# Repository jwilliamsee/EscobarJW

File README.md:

# EscobarJW
Todo el texto no está justificado porque el formato Markdown usado en esta plataforma no lo permite, en algunos párrafos si está justificado porque uso html pero en algunas estructuras de texto aquí presentadas no es posible aplicarlo.
### Información.

#### En la carpeta "**Certificado-Ingeniería**"

<p align="justify">Está el certificado de estudios de la carrera universitaria en Ingeniería Electromecánica con especialidad en la industria aeroespacial, específicamente enfocado a diseño CAD y electrónica.</p>

------------
#### En la carpeta "**LoQueHiceEn-IER-UNAM**". 
<p align="justify">Se encuentran 7 dispositivos electrónicos en los que participé durante la residencia profesional y posteriormente con un contrato laboral para seguir colaborando, lo planteado inicialmente era establecer una forma de documentar los dispositivos electrónicos que se tenían avanzados, con un estándar de documentación que se adaptara a etapas de desarrollo enfocado a documentar todo lo que se había hecho y faltaba por hacer en cada uno. El problema a solucionar era que cuando otros estudiantes llegaban para hacer residencias o prácticas profesionales y avanzaban en alguno de los dispositivos, no dejaban documentación completa de lo que avanzaban o no entregaban algo de lo que hacían, los diagramas estaban incompletos o estaban pero no los archivos fuentes para editar y modicar, los códigos de programación no estaban para editarlos y se tenía que contactar al estudiante que lo empezó y con suerte rescatarlo para futuras mejoras, el hardware se tenía que reconectar y reestructurar y pasar por los mismos errores que quizá pasó el primer estudiante en las primeras versiones y a todo eso con el estándar de documentación que investigué y finalmentente elegí con algunas adaptaciones necesarias para lo que se requería, hicieron que mis aportaciones fueran las siguientes:.</p>

	Solución y aportes propuestos por mi:
- [x] Investigación y elección del estándar de documentación para los dispositivos electrónicos del IER-UNAM.
- [x] Elección de la forma de documentación en cuanto a Hardware adaptada al estándar "Open-Know-How".
[**Open-Know-How**](https://www.internetofproduction.org/open-know-how)
- [x] Gestionar la documentación en todos los dispositvos hechos y por hacer, para el control y cumplimiento de cada avance hechos por otros compañeros.
- [x] Apliqué el estándar de documentación a un dispositivo como prueba y posteriormente se usó como ejemplo para que los otros compañeros lo aplicaran al dispositivo que estaban desarrollando.
- [x] Instructivos para documentar sus avances en esta plataforma en forma de repositorio por cada dispositivo desde Windows y Linux.
- [x] Apoyo de todo el proceso para documentar, con videos del paso a paso.
[**Serie de videos hechos por mi**](https://github.com/jwilliamsee/DocumentarGithub/blob/main/VideosDocGit/LinksDeVideos.md)

**Cabe mencionar que en cada dispositivo participó más de una persona, yo participé en todos para verificar que se aplicara lo que propuse, apoyar en las dudas de como documentar con el estándar elegido, probar y modificar código básico en Python, C++ y Micropython (yo no programaba), mis participaciones también se centraban en la parte del Hardware electrónico.**
- [x] Al mismo tiempo de la investigación, desarrollo, aplicación del estándar y seguimiento a cada dispositivo, también me ocupaba en el desarrollo del dispositivo H2O, sólo se tenía el código o programación. [**Dispositivo H2O**](https://github.com/jwilliamsee/EscobarJW/tree/main/LoQueHiceEn-IER-UNAM/SensorH2O1)
- [x] Diseñé la carcasa del dispositivo H2O, diseñé la placa PCB, hice el diagrama de conexión, diagrama de conexión animada (pictograma), modifiqué la programación, generé archivos para impresión en 3D, instructivo de uso del dispositivo, instructivo de ensamble, pruebas del funcionamiento y los archivos entregables.
------------
## Parte de mi trabajo en el IER-UNAM
<p align="justify">Durante el tiempo que trabajé en el **Instituto de Energías Renovables** (IER-UNAM), posterior a los 6 meses que estuve en residencia profesional, seguí trabajando en los dispositivos, hasta liberar documentación necesaria en cada uno, modificar archivos trabajados por otros compañeros, pruebas de mando a distancia con una plataforma Internet Of Things (IOT), entre otras cosas.<p/>

#### A continuación una breve descripción de cada dispositivo en los que apoyé y lo que aporté:
	Dispositivo DTHIS: Mide Temperatura, Humedad, Iluminación y Sonido (nivel sonoro).
[**Dispositivo DTHIS**](https://github.com/jwilliamsee/EscobarJW/tree/main/LoQueHiceEn-IER-UNAM/DTHIS)

**Aportes:**
- Gestión de la documentación.
- Diseño de PCB como complemento del existente.
- Rediseño del diagrama de conexión.
- Réplica de un segundo dispositivo DTHIS para comprobar que ya era factible y viable su reprodución (funcionó correctamente el segundo).
------------
	Dispositivo FactorDePotencia: Mide Factor de potencia y consumo de energía eléctrica.
[**Dispositivo FactorDePotencia**](https://github.com/jwilliamsee/EscobarJW/tree/main/LoQueHiceEn-IER-UNAM/FactorDePotencia)

**Aportes:**
- Avances en la gestión de documentación.
- Diseño CAD de la carcasa del dispositivo.
- Rediseño del PCB existente.
- Diseño del diagrama de conexión.
------------
	Repositorio TemplateSADs: Plantilla para usarlo en la documentación de otros dispositivos.
[**Repositorio TemplateSADs**](https://github.com/jwilliamsee/EscobarJW/tree/main/LoQueHiceEn-IER-UNAM/TemplateSADs)

**Aportes:**
###### Formato elegido, previamente investigado para ser adaptado a otros dispositivos.
------------
	 Dispositivo WindSensor: Mide la rapidez del viento.
[**Dispositivo WindSensor**](https://github.com/jwilliamsee/EscobarJW/tree/main/LoQueHiceEn-IER-UNAM/WindSensor)

**Aportes:**
- Investigación de la implementación del sensor elegido.
- Modificar la programación para lectura del viento (ya existía un reporte trabajado).
- Diagrama de conexión.
- Pruebas de su funcionamiento bajo condiciones necesarias de operación.
- Montaje de banco de prueba básico.
------------
	Dispositivo abb_energia: Equipo industrial que mide corriente eléctrica trifásica, factor de potencia, potencia activa, potencia aparente, potencia reactiva y voltaje.
[**Dispositivo abb_energia**](https://github.com/jwilliamsee/EscobarJW/tree/main/LoQueHiceEn-IER-UNAM/abb_energia)

**Aportes:**
- Gestión de la documentación (revisión).
- Asesoría en la documentación.
------------
	 Dispositivo sensor_flujo_calor: Mide el flujo de calor de superficies planas con ciertas condiciones.
[**Dispositivo sensor_flujo_calor**](https://github.com/jwilliamsee/EscobarJW/tree/main/LoQueHiceEn-IER-UNAM/sensor_flujo_calor)

**Aportes:**
- Gestión de la documentación (revisión).
- Asesoría en la documentación.
------------

##### Existen otros dispositivos y repositorios que ya no están en mi dominio, de igual forma estos dispositivos que se presentan se siguieron avanzando y participé en la gestión de documentación, manufactura, diseño, étc.
------------

####  En la carpeta "Proyecto_Residencia_Profesional" se encuentra el reporte de residencia que entregué al Instituto Tecnológico de Ensenada (ITE) y las evaluacioenes de la misma, por el Dr. Barrios, mi jefe inmediato durante la residencia, también se encuentra la carta de término de residencia emitida por el Instituto de Energías Renovables (IER-UNAM).
[**Reporte de residencia profesional**](https://github.com/jwilliamsee/EscobarJW/tree/main/Proyecto_ResidenciaProfesional)

------------

####  En la carpeta "Proyecto_ServicioSocial" se encuentran archivos del proyecto que propuse durante el servicio social: "Cálculo de cargas térmicas para la elección adecuada del sistema de aire acondicionado", al ver una oportunidad de mejora en la biblioteca del Instituto Tecnológico de Ensenada por el exceso de calor que se acumulaba y no contar con aire acondicionado.
#### El objetivo principal del proyecto fue calcular la carga térmica total de la planta baja del centro de información, para diseñar un ambiente de confort, los resultados son cálculos en toneladas de refrigeración para elegir los equipos comerciales de aire acondicionado y las posibles distribuciones de los mismos en la planta baja, se entregó un reporte técnico y la memoria de cálculo para ser considerado al momento de acondicionar la biblioteca y no sobredimensionar en exceso los equipos y que posteriormente represente un exceso en el consumo de energía eléctrica. El proyecto está relacionado con **Refrigeración, aire acondicionado** y **Transferencia de calor**.

[**Proyecto servicio social**](https://github.com/jwilliamsee/EscobarJW/tree/main/Proyecto_ServicioSocial)

**Aportes:**
- [x] Cálculo de cargas térmicas por infiltración.
- [x] Cálculo de cargas térmicas por radiación.
- [x] Cálculo de cargas térmicas por equipos.
- [x] Cálculo de condiciones de confort con tablas psicométricas.
- [x] Entrega de memoria de cálculos en Excel.
- [x] Recomendaciones en la elección de los equipos de aire acondicionado.

------------
# Algunos diseños CAD, diagramas electrónicos y Diseño PCB en los que he trabajado, existen otros PCB que por confidencialidad de mi empleador freelancer no puedo mostrar:

### Máquina de serigrafía
#### Diseño de máquina para serigrafía con ecuaciones de movimiento.

------------

------------
### Dispositivo THIS
#### Diagrama de conexión electrónica del dispositivo THIS, parte del trabajo en el IER-UNAM:

------------
#### Pictograma de conexión (conexión animada) del mismo dispositivo THIS:

------------
#### Montaje en pruebas del dispositivo THIS:

------------
#### Diseño de PCB como complemento del dispositivo THIS:

------------
### Dispositivo factor de potencia
#### Rediseño de PCB del dispositivo Factor de potencia, parte del trabajo en el IER-UNAM:

------------
#### Diseño CAD de carcasa del dispositivo Factor de potencia, parte del trabajo en el IER-UNAM:

------------
### Dispositivo H2O
#### Diseño CAD de la carcasa del dispositivo H2O

------------

------------

------------
#### Diagrama electrónico del dispositivo H2O

------------
#### Diseño PCB del dispositivo H2O

------------
#### Representación general para el diseño del dispositivo H2O

------------
#### Planos de la carcasa del dispositivo H20

------------

------------
### Trabajando como Freelancer en tiempos libres
#### Diseño de PCB1

------------

------------
#### Diseño de PCB2

------------

------------
### Simulación de análisis estático
#### Análisis estático de una caldera

------------

------------

------------

------------

------------

------------
#### Análisis estático de un sujetador mecánico 

------------

------------

------------

------------

------------

------------

------------

------------

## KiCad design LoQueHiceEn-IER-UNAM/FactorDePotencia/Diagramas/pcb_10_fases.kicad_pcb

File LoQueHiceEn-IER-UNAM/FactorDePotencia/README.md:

# Dispositivo Factor de potencia

# 1.0 Introducción

El futuro de la humanidad y del planeta dependen de la manera en la que produzcamos energía: un sistema energético fiable, asequible y descarbonizado es fundamental.
Las energías renovables son fuentes de energía limpias, inagotables y crecientemente competitivas. Se diferencian de los combustibles fósiles principalmente en su diversidad, abundancia y potencial de aprovechamiento en cualquier parte del planeta, pero sobre todo en que no producen gases de efecto invernadero, causantes del cambio climático, ni emisiones contaminantes. Además, sus costes evolucionan a la baja de forma sostenida, mientras que la tendencia general de costes de los combustibles fósiles es la opuesta.
El crecimiento de las energías renovables es imparable, como queda reflejado en las estadísticas aportadas anualmente por la Agencia Internacional de la Energía (AIE): según las previsiones de la AIE, la participación de las renovables en el suministro eléctrico global pasará del 26% en 2018 al 44% en 2040, y proporcionarán 2/3 del incremento de demanda eléctrica registrado en este período, principalmente a través de las tecnologías eólica y fotovoltaica.
De acuerdo a la AIE, la demanda mundial de electricidad aumentará un 70% hasta 2040, elevando su participación en el uso de energía final del 18% al 24% en el mismo período, espoleada principalmente por regiones emergentes (India, China, África, Oriente Medio y el Sureste asiático).
Con lo anterior y compartiendo la idea de utilizar mas las energías limpias, se implementan nuevas formas de controlar los diferentes recursos que se utilizan en el día a día en el Instituto de Energías Renovables-UNAM, se implementarán dispositivos que puedan medir la cantidad de recursos que se consumen como lo son: el agua, la energía eléctrica, humedad, intensidad luminosa, temperatura, entre otras, de un edificio del instituto, con la intención de poder medir cada variable y posteriormente observar cuanto se consume para tratar de reducirlos en gran medida, lo anterior se lleva a cabo con dispositivos electrónicos que están integrados principalmente con sensores y haciendo uso de tecnologías abiertas para los programas y envío de datos a la plataforma IOT Thingsboard para la visualización de gráficos.

### 1.1 Sobre los autores

|Nombre|Instituto/Organización|Email|
| ------------ | ------------ | ------------ |
|Juan Valle Bahena|ITZ|juanvb999@gmail.com|
|Falta |Falta|Falta|
|Guillermo Barrios del Valle|IER-UNAM|gbv@ier.unam.mx|
|Guillermo Ramírez Zúñiga|IER-UNAM|guraz@ier.unam.mx|

------------

# 2. Alcance

El dispositivo Factor de potencia tiene como alcance, en esta etapa, contar con toda la documentación necesaria  e incluso en atapa inicial de pruebas, después de ser trabajado por un grupo de personas se espera que el proyecto tenga todo lo que se necesita para que otras personas puedan entender el funcionamiento y requisitos de operación.

La audiencia a la que está destinada es:

- Por el momento a personal del IER-UNAM que se encuentra trabajando en el proyecto "Edificios demostrativos de diseño bioclimático en clima cálido subhúmedo en el Instituto de Energías Renovables UNAM".

Proyecto número 291600 del Fondo de Sustentabilidad Energética.
- Compañeros que se interesen en aportar al proyecto para mejorar o para replicarlo directamente.

------------

# 3. Conceptos y definiciones

### 3.1 Saber como

Es necesario conocer algunas cosas antes de intentar entender muchos puntos del proyecto, como por ejemplo: lectura de planos electrónicos, diseño CAD, conocimiento medio de electrónica, programación, entre otras.

### 3.2 Diseño

Deberá manejar algún software de diseño por computadora, para modificar, replicar el diseño existente e incluso conocer la sección de ensamble de piezas en el software de su preferencia.

### 3.3 Hacer

Fabricar, construir, ensamblar, imprimir, configurar, programar y compilar códigos.

### 3.4 Open source

Por su traducción al español, "fuente abierta" durante el desarrollo del proyecto se busca que todos los programas a usar, sean de fuente abierta para evitar pagos costosos de Licencia, para cada necesidad existe un software de fuente abierta.

### 3.5 Thingsboard

Es una plataforma de IOT que nos ayuda a visualizar gráficamente las variables que se están midiendo para tener referencias de lo que se está haciendo.

### 3.6 Github

Plataforma web, que sirve como "bodega" para almacenar un proyecto con sus respectivas versiones o modificaciones que pueda sufirir durante el desarrollo, al mismo tiempo ayuda a documentar y a entender la estructura de su funcionamiento.

------------

# 4.0 Especificaciones de la estructura

### 4.1 Introducción

En esta sección se encuentra la estructura general del proyecto, de forma que sea entendible y que se le pueda dar seguimiento para la lectura del mismo y entender que lleva un orden.
Esta forma de estructurar el proyecto es un formato estándar de Open Know-How, cabe mencionar que no es el ideal pero para entender de forma general un proyecto de electrónica es aceptable.
El almacenamiento en Github nos ayuda en todo momento a realizar modificaciones que creemos necesarias y sobre todo a tener control total de los cambios que va sufriendo el proyecto durante el desarrollo, si alguna no nos agrada o no es la correcta, podemos regresar sin ningún problema y dejarlo como antes.

### 4.2 Estructura

### 4.2.1 Formato

El formato de archivo para la documentación del dispositivo es Markdown por su facilidad de uso.
Algunos archivos están en formato PDF pero es necesario para una mejor visualización de los esquemas que se muestran en ese formato.

### 4.2.2 Nombre del archivo

Para los nombres de los archivos, es necesario que no se usen comas, virgulilla o tilde de la ñ, las separaciones de las palabras pueden ser usadas con guiones o sin espacios, pero con una letra mayúscula para saber donde termina e inicia otra palabra, por ejemplo: ArchivoEstructura".
Las extensiones de los archivos pueden ser:

- .json | Para los archivos que se realizaron con EasyEDA.
- .md | Para los archivos que son creados en formato de texto Markdown, M Editor, DILLINGER e incluso el archivo README de Github.
- .fzz | Para los archivos que fueron creados en el software de Fritzing, pictogramas de conexiones.
- .ESTEP | Para los archivos de diseño CAD, que pueden ser visualizados en cualquier software de diseño, es formato general.
- .STL | Para los archivos de impresión, para que el diseño de la carcasa del dispositivo pueda ser visualizado al momento de imprimirlo en 3D.
- .zip | Para los archivos de impresión de la placa o PCB, están comprimidos porque son varios archivos.
- .PDF | Para los archivos que si se guardan en otro formato, posiblemente se moverían mucho las líneas, formas, tablas, imágenes, etc. Los archivos que se encontrarán en el repositorio en este formato serán los planos para el diseño de la carcasa.

### 4.2.3 Vínculos

En algunas secciones de la documentación es necesario nombrar o hacer referencias a rutas externas, pueden ser a imágenes, páginas web entre otras, simplemente se hace uso de los links originales de la web en cuestión, copiando y posteriormente pegando en la sección correspondiente para no tener que buscar de manera externa, deberán dejar espacios entre título o texto para que no existan errores de posición en el archivo de texto final.

#### 4.2.4 Ubicación del repositorio

El repositorio de todo el proyecto se encuentra en Github, las diferentes carpetas y archivos están alojadas en un un solo repositorio, no existe una carpeta raíz, pero sí existe una dirección raíz y es la siguiente:

[**Falta redireccionarlo**]()

### 4.3 Información de la web

La página de presentación del proyecto, está en la sección de Github.

El sitio web del formato estándar para documentar es el siguiente:

[**Falta redireccionarlo**]()

### 4.4 Propiedades descriptivas

### 4.4.1 Título

##### Dispositivo de Factor de potencia
##### Medidor de.....(falta complementar)

### 4.4.2 Descripción

##### Energías renovables
##### Dispositivo pensado para...(falta complementar)

### 4.4.3 Uso previsto

##### Control de variable
###### Informa al usuario el....(falta complementar)

### 4.4.4 Palabras clave

##### Electrónica
##### Dispositivo
##### Faltan poner otras

### 4.4.5 Precauciones y recomendaciones

Son recomendaciones para operar el dispositivo(falta complementar)

### 4.5.6 Contacto primario

**Inv. A tiempo completo:** Dr. Guillermo Barrios del Valle

**Email:** gbv@ier.unam.mx

**Posdoc.:** Dr. Guillermo Ramírez Zúñiga

**Email:** guraz@ier.unam.mx

### 4.5.7 Colaboradores

**Nombre: Juan Valle Bahena** 

**Instituto: Instituto Tecnológico de Zacatepec (ITZ)**

**Email: juanvb999@gmail.com**

**Nombre:**

**Instituto:**

**Email:**

**Nombre:**

**Instituto:**

**Email:**

### 4.5.7 Imagen

Representación gráfica del dispositivo Factor de potencia (**Falta**)

### 4.5.8 Etapa de desarrollo

La etapa en la que se encuentra el desarrollo del dispositivo Factor de potencia, es la de documentación y primeras pruebas.

## Seguimiento de actividades del dispositivo Factor de potencia

|**Actividad**|**Tiempo estimado de ejecución**|**% de avance**|**Pendientes**|**Notas**   |
| :------------: | :------------: | :------------: | :------------: | :------------: |
|**1.**| |   |   |   |
|   |   |   |   |   |
|**2.**|   |   |   |   |
|   |   |   |   |   |
|**3.**|   |   |   |   |
|   |   |   |   |   |
|**4.**|   |   |   |   |
|   |   |   |   |   |
|**5.**|   |   |   |   |
|   |   |   |   |   |
|**6.**|   |   |   |   |
|   |   |   |   |   |
|**7.**|   |   |   |   |
|   |   |   |   |   |
|**8.**|   |   |   |   |
|   |   |   |   |   |
|**9.**|   |   |   |   |
|   |   |   |   |   |
|**10.**|   |   |   |   |
|   |   |   |   |   |
|**11.**|   |   |   |   |
|   |   |   |   |   |
|**12.**|   |   |   |   |
|   |   |   |   |   |
|**13.**|   |   |   |   |
|   |   |   |   |   |
|**14.**|   |   |   |   |
|   |   |   |   |   |
|**15.**|   |   |   |   |
|   |   |   |   |   |
|**16.**|   |   |   |   |
|   |   |   |   |   |
|**17.**|   |   |   |   |
|   |   |   |   |   |
|**18.**|   |   |   |   |
|   |   |   |   |   |
|**19.**|   |   |   |   |
|   |   |   |   |   |
|**20.**|   |   |   |   |
|   |   |   |   |   |

------------

## CHECK-LIST de lo que debe tener el dispositivo
- [ ] Lista de costos
- [ ] SRC completos
- [ ] Pictograma de conexión
- [ ] Esquemático de conexión
- [ ] Archivos de diseño PCB
- [ ] Archivos gerber para el maquinado del PCB
- [ ] Lista de materiales
- [ ] Planos CAD
- [ ] Archivos de diseño CAD
- [ ] Archivos STL para impresión 3D
- [ ] Manual de operación
- [ ] Manual de ensamble
- [ ] Fichas técnicas o datasheet de los módulos, sensores y componentes usados
- [ ] Documento de errores, soluciones y recomendaciones

### 4.5.9 Fue hecho físicamente

El dispositivo aún no se ha hecho de forma práctica en su totalidad, es decir, no se ha llevado a la práctica para comprobar el funcionamiento del dispostivo completo con todos sus componentes.

### 4.5.10 Se ha comprobado la documentación

La réplica del dispositivo usando la estructura aquí mostrada y siguiendo la documentación no se ha realizado, aún está en revisión de estructura de documentación y de archivos factibles para el desarrollo eficiente.

### 4.5.11 Estándares usados

El estándar de documentación completo, no se ha seguido, pero si se ha usado el estándar para esta documentación de Open Know-How, algunos puntos se han omitido porque al no ser la estructura para documentar proyectos electrónicos, existen puntos que salen sobrando o que definitivamente no aplican para este tipo de proyectos.
El link del estándar usado es el siguiente:

[EstandarOpenKnowHow](https://app.standardsrepo.com/MakerNetAlliance/OpenKnowHow/src/branch/master/1#a40dfa47-8bff-4e28-9338-3f808ddfe6ae)

### 4.6 Documentación

### 4.6.1 Punto de entrada de la documentación:

### Carpeta [CAD](https://github.com/Dispositivos-Edificio-Bioclimatico/FactorDePotencia/tree/master/CAD)

En la carpeta CAD se deben poner los archivos .STEP del diseño de la carcasa o de alguna parte física.

En la misma carpeta se deben poner planos en formato PDF y los archivos .STL para visualización.

### Carpeta [Diagramas](https://github.com/Dispositivos-Edificio-Bioclimatico/FactorDePotencia/tree/master/Diagramas)

En la carpeta de Diagramas se debe poner, el esquemático, el diseño de PCB, representaciones gráficas de conexión (pictogramas) y archivo gerber con lo necesario para maquinar el pcb.

### Carpeta [Imagenes](https://github.com/Dispositivos-Edificio-Bioclimatico/FactorDePotencia/tree/master/Imagenes)

En esta carpeta deben ir todas las imagenes que se usaron en los archivos de los manuales y otras imagenes necesarias para el complemento del dispositivo.

### Carpeta [Manuales](https://github.com/Dispositivos-Edificio-Bioclimatico/FactorDePotencia/tree/master/Manuales)

En esta carpeta se debe contener lo siguiente:
1. El manual de operación, para consultarlo antes de iniciar con la replica del dispositivo.
2. El manual de ensamble, de manera gráfica (ilustrativa), se describe de forma general como realizar el ensamble de los componentes del dispositivo.
3. Un manual de errores y soluciones que debe tener algunas sugerencias de operación para operar el dispositivo.

### Carpeta [Materiales](https://github.com/Dispositivos-Edificio-Bioclimatico/FactorDePotencia/tree/master/Materiales)

En la carpeta "Materiales" se deben poner los archivos con extensión md y otros en PDF.
1. En el archivo Lista_de_materiales_Ejem se encuentran los materiales que ne necesitan para el pcb. (es de ejemplo, debe adaptarse)
2. En el archivo ListaCostosEjem se encuentran los costos unitarios y total de los componentes. (es de ejemplo, debe adaptarse)
3. Los archivos en PDF son hojas de datos de algunos componentes que se usan en el dipositivo. (deben ir de todos los compenentes usados)

### Carpeta [SRC](https://github.com/Dispositivos-Edificio-Bioclimatico/FactorDePotencia/tree/master/SRC)

En esta carpeta deberán ponerse todos los códigos necesarios para operar el dispositivo y debe ponerse un archivo de texto donde explique, lo que hace cada código en la carpeta. (hay uno básico de ejemplo, deberá adaptarse)

### Thingsboard

Aquí debe ir información del dispositivo para visualizar datos en la plataforma IOT Thingsboard, credenciales, dashboard, nombre del dispositivo en la plataforma y todo lo que tenga que ver con la comunicación del dispositivo y Thingsboard.

------------

# 5.0 Bibliografía

[1] **Open Know-How**
https://app.standardsrepo.com/MakerNetAlliance/OpenKnowHow/src/branch/master/1#a40dfa47-8bff-4e28-9338-3f808ddfe6ae

[2] **Github**
https://github.com/

[3] **DILLINGER**
https://dillinger.io/

[4] **M Editor.md**
https://pandao.github.io/editor.md/en.html

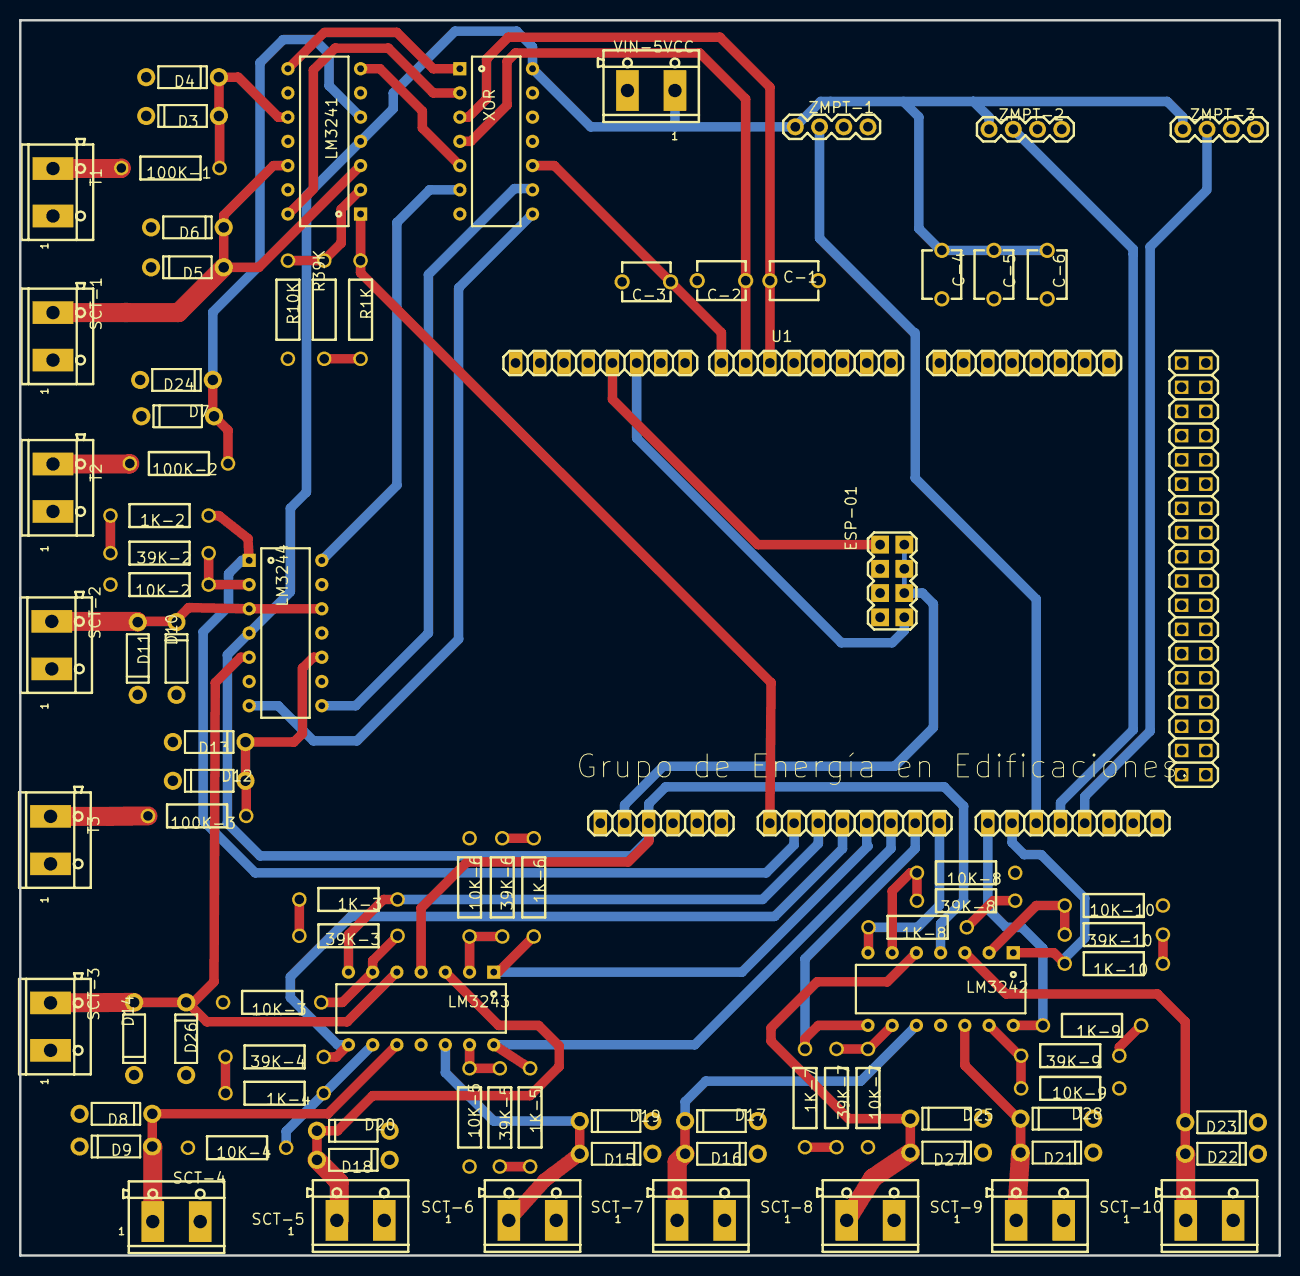
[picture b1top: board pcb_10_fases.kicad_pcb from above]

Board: 2 copper layers, 132.1 x 129.5 mm, 89 parts (0 on the bottom side), 56 nets.

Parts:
1K-2, 1K-3, 1K-4, 1K-5, 1K-6, 1K-7, 1K-8, 1K-9, 1K-10, 10K-2, 10K-3, 10K-4, 10K-5, 10K-6, 10K-7, 10K-8, 10K-9, 10K-10, 39K-2, 39K-3, 39K-4, 39K-5, 39K-6, 39K-7, 39K-8, 39K-9, 39K-10, 100K-1, 100K-2, 100K-3: RES-TH_BD2.4-L6.3-P10.30-D0.6
C-1, C-2, C-3, C-4, C-5, C-6: CAP-TH_L5.0-W4.0-P5.00-D1.0
D3, D4, D5, D6, D7, D8, D9, D10, D11, D12, D13, D14, D15, D16, D17, D18, D19, D20, D21, D22, D23, D24, D25, D26, D27, D28: DO-35
ESP-01: 2X4
LM3241, LM3242, LM3243, LM3244: DIP14
R1K, R10K, R39K: RES-TH_BD2.4-L6.3-P10.30-D0.6
SCT-1, SCT-2, SCT-3, SCT-4, SCT-5, SCT-6, SCT-7, SCT-8, SCT-9, SCT-10: 1; TERMINAL_BLOCK_2P_5
T1, T2, T3: 1; TERMINAL_BLOCK_2P_5
U1: MEGA_ARDUINO_2
VIN-5VCC: 1; TERMINAL_BLOCK_2P_5
XOR: DIP14
ZMPT-1, ZMPT-2, ZMPT-3: 1X04-BIG

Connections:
GND: 10K-2.1, 10K-3.1, 10K-4.1, 10K-5.1, 10K-6.2, 10K-7.1, 10K-8.2, 10K-9.2, 10K-10.2, C-1.2, C-2.1, C-3.1, C-4.1, C-5.1, C-6.1, D3.2, D4.1, D5.2, D6.1, D7.2, D10.2, D11.1, D12.2, D13.1, D14.2, D15.2, D16.2, D17.1, D18.2, D19.1, D20.1, D21.2, D22.2, D23.2, D24.1, D25.1, D26.1, D27.2, D28.1, ESP-01.7, LM3241.6, LM3241.9, LM3241.11, LM3241.13, LM3242.11, LM3243.11, LM3244.6, LM3244.9, LM3244.11, LM3244.13, R10K.1, SCT-1.1, SCT-2.1, SCT-3.1, SCT-4.1, SCT-5.1, SCT-6.1, SCT-7.1, SCT-8.1, SCT-9.1, SCT-10.1, T1.1, T2.1, T3.1, U1.4, U1.5, VIN-5VCC.2, XOR.7, ZMPT-1.3, ZMPT-1.4, ZMPT-2.3, ZMPT-2.4, ZMPT-3.3, ZMPT-3.4
S$2705: 100K-1.1, T1.2
S$2707: 100K-1.2, D3.1, D4.2, LM3241.10
S$2727: D5.1, D6.2, LM3241.3, LM3241.12, SCT-1.2
S$2733: LM3241.14, XOR.2
S$3126: LM3241.2, R10K.2, R39K.1
S$3129: R1K.1, R39K.2
S$3199: 100K-2.1, T2.2
S$3249: U1.36, XOR.3
S$3313: 100K-2.2, D7.1, D24.2, LM3241.5
S$3334: LM3241.7, XOR.5
S$3339: D10.1, LM3244.3, LM3244.12, SCT-2.2
S$3345: 10K-2.2, 39K-2.2, LM3244.2
S$3348: 1K-2.1, 39K-2.1
S$3350: 1K-2.2, LM3244.1, U1.8
S$3353: LM3244.14, XOR.6
S$3375: LM3244.8, XOR.9
S$3405: D14.1, D26.2, LM3243.5, LM3244.5, SCT-3.2
S$4354: U1.37, XOR.4
S$4365: 1K-3.2, LM3243.7, U1.9
S$4400: 1K-3.1, 39K-3.1
S$4411: U1.38, XOR.10
S$4418: D8.2, D9.1, LM3243.10, SCT-4.2
S$4433: LM3243.8, U1.10
S$4450: D18.1, D20.2, LM3243.3, SCT-5.2
S$4457: 10K-5.2, 39K-5.2, LM3243.13
S$4460: 1K-5.1, 39K-5.1
S$4462: 1K-5.2, LM3243.14, U1.12
S$4466: D15.1, SCT-6.2
S$4529: D19.2, LM3243.12
S$4531: 10K-6.1, 39K-6.1, LM3243.2
S$4534: 1K-6.2, 39K-6.2
S$4536: 1K-6.1, LM3243.1, U1.11
S$4552: D16.1, D17.2, LM3242.10, SCT-7.2
S$4559: 10K-7.2, 39K-7.2, LM3242.9
S$4562: 1K-7.1, 39K-7.1
S$4564: 1K-7.2, LM3242.8, U1.13
S$4663: D25.2, D27.1, LM3242.5, SCT-8.2
S$4669: 10K-8.1, 39K-8.1, LM3242.6
S$4672: 1K-8.2, 39K-8.2
S$4674: 1K-8.1, LM3242.7, U1.14
S$4679: D21.1, D28.2, LM3242.12, SCT-9.2
S$4742: 10K-9.1, LM3242.13
S$4745: 1K-9.2, 39K-9.2
S$4747: 1K-9.1, LM3242.14, U1.15
S$4750: D22.1, D23.1, LM3242.3, SCT-10.2
S$4755: 10K-10.1, 39K-10.1, LM3242.2
S$4758: 1K-10.2, 39K-10.2
S$4760: 1K-10.1, LM3242.1, U1.16
S$4992: ESP-01.2, ESP-01.4, ESP-01.6, U1.2
S$4998: ESP-01.8, U1.41
S$5000: ESP-01.1, U1.42
S$5174: U1.17, ZMPT-1.2
S$5176: U1.18, ZMPT-2.2
S$5178: U1.19, ZMPT-3.2
S$6595: C-4.2, C-5.2, C-6.2, LM3241.4, LM3242.4, LM3243.4, LM3244.4, U1.3, VIN-5VCC.1, XOR.14, ZMPT-1.1, ZMPT-2.1, ZMPT-3.1

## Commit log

2022-02-28 agregué carpetas
2022-03-01 agregué carpeta
2022-06-10 agregue carpeta
2022-08-26 agregué constancia
2023-01-12 Constancia de Ingles 2023
2023-01-17 ConstanciaPSpiceBasico
2023-02-12 modifique texto
2023-02-15 Update text
2023-02-23 delete
2023-03-14 Delete1
2023-03-14 Delete2
2023-04-07 Actualice
2023-05-15 UpdateTextAboutIpython123
2023-05-16 Deletefilering
2023-05-16 Deletefilecert
2023-06-13 UpdateReadme.md
